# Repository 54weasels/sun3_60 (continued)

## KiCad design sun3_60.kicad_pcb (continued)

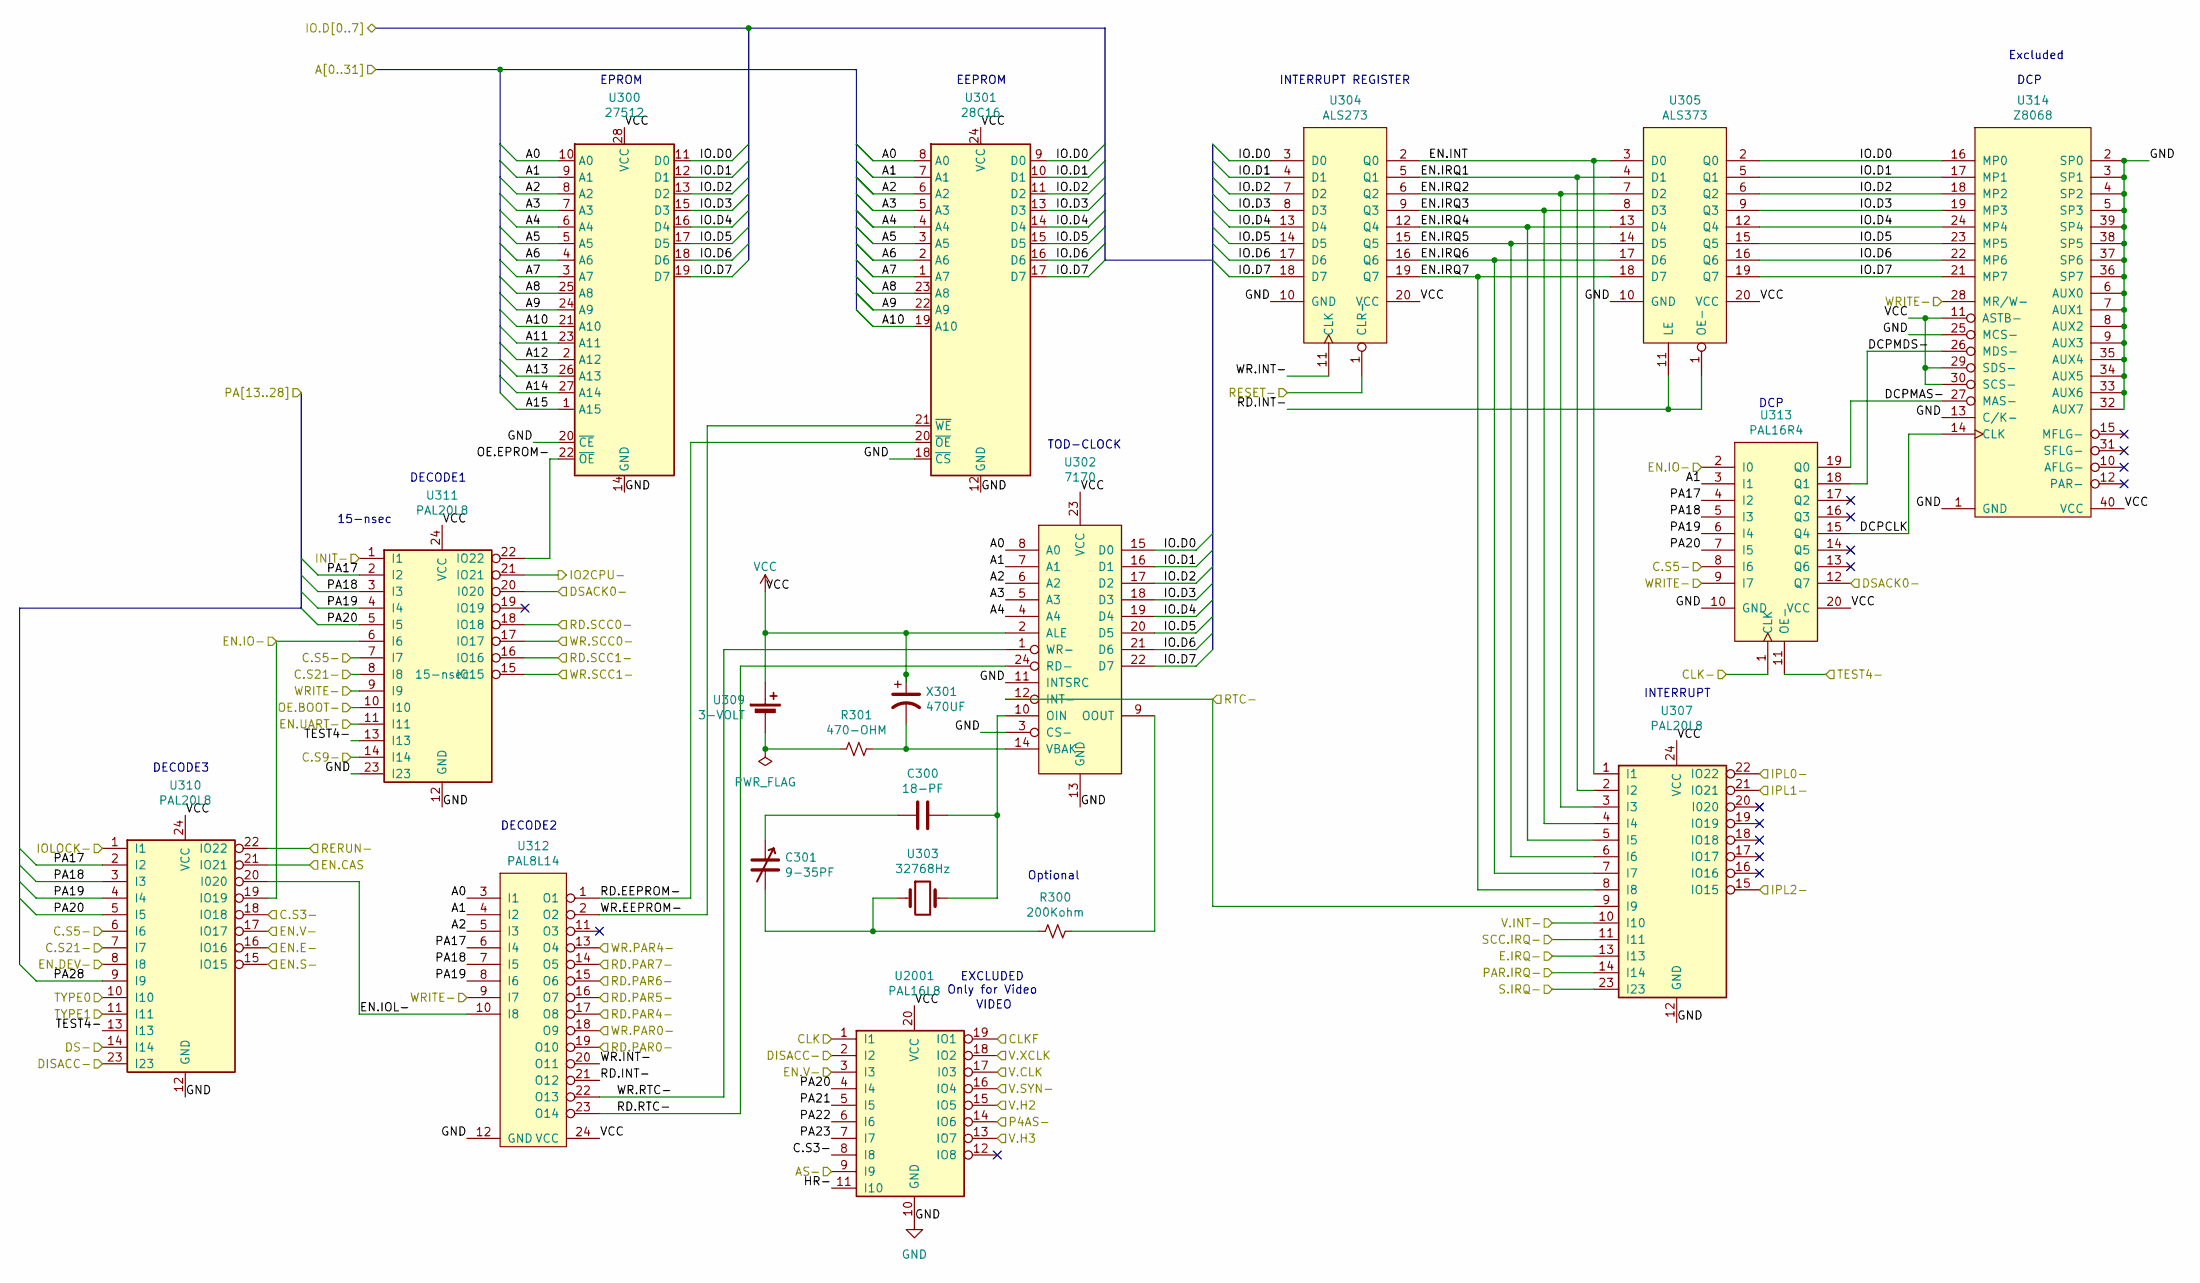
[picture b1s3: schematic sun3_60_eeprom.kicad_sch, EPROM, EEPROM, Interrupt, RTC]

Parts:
C300: 18-PF; C_Disc_D3.0mm_W2.0mm_P2.50mm
C301: 9-35PF; C_Radial_D6.3mm_H5.0mm_P2.50mm
R300: 200Kohm; R_Axial_DIN0207_L6.3mm_D2.5mm_P7.62mm_Horizontal
R301: 470-OHM; R_Axial_DIN0207_L6.3mm_D2.5mm_P7.62mm_Horizontal
U300: 27512; DIP-28_W15.24mm
U301: 28C16; DIP-24_W15.24mm
U302: 7170; DIP-24_W15.24mm
U303: 32768Hz; Crystal_AT310_D3.0mm_L10.0mm_Horizontal
U304: ALS273
U305: ALS373
U307, U310, U311: PAL20L8; DIP-24_W7.62mm
U309: 3-VOLT; Battery_Panasonic_CR2032-VS1N_Vertical_CircularHoles
U312: PAL8L14; DIP-24_W7.62mm
U313: PAL16R4; DIP-20_W7.62mm
U314: Z8068; DIP-40_W15.24mm
U2001: PAL16L8; DIP-20_W7.62mm
X301: 470UF; CP_Radial_D10.0mm_P5.00mm

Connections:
/C.S3-: U310.18 (IO18); also elsewhere on the board
/CLK-: U313.1 (CLK); also elsewhere on the board
/DISACC-: U310.23 (I23), U2001.2 (I2); also elsewhere on the board
/DS-: U310.14 (I14); also elsewhere on the board
/DSACK0-: U311.20 (I020), U313.12 (Q7); also elsewhere on the board
/E.IRQ-: U307.13 (I13); also elsewhere on the board
/EN.CAS: U310.21 (IO21); also elsewhere on the board
/EN.DEV-: U310.8 (I8); also elsewhere on the board
/EN.E-: U310.16 (IO16); also elsewhere on the board
/EN.UART-: U311.11 (I11); also elsewhere on the board
/Ethernet/A0: U300.10 (A0), U301.8 (A0), U302.8 (A0), U312.3 (I1); also elsewhere on the board
/Ethernet/A1: U300.9 (A1), U301.7 (A1), U302.7 (A1), U312.4 (I2), U313.3 (I1); also elsewhere on the board
/Ethernet/A2: U300.8 (A2), U301.6 (A2), U302.6 (A2), U312.5 (I3); also elsewhere on the board
/Ethernet/A3: U300.7 (A3), U301.5 (A3), U302.5 (A3); also elsewhere on the board
/Ethernet/A4: U300.6 (A4), U301.4 (A4), U302.4 (A4); also elsewhere on the board
/Ethernet/A5: U300.5 (A5), U301.3 (A5); also elsewhere on the board
/Ethernet/A6: U300.4 (A6), U301.2 (A6); also elsewhere on the board
/Ethernet/A7: U300.3 (A7), U301.1 (A7); also elsewhere on the board
/Ethernet/A8: U300.25 (A8), U301.23 (A8); also elsewhere on the board
/Ethernet/A9: U300.24 (A9), U301.22 (A9); also elsewhere on the board
/Ethernet/A10: U300.21 (A10), U301.19 (A10); also elsewhere on the board
/Ethernet/A11: U300.23 (A11); also elsewhere on the board
/Ethernet/A12: U300.2 (A12); also elsewhere on the board
/Ethernet/A13: U300.26 (A13); also elsewhere on the board
/Ethernet/A14: U300.27 (A14); also elsewhere on the board
/Ethernet/A15: U300.1 (A15); also elsewhere on the board
/INIT-: U311.1 (I1); also elsewhere on the board
/IO2CPU-: U311.21 (IO21); also elsewhere on the board
/IOLOCK-: U310.1 (I1); also elsewhere on the board
/IPL0-: U307.22 (IO22); also elsewhere on the board
/IPL1-: U307.21 (IO21); also elsewhere on the board
/IPL2-: U307.15 (IO15); also elsewhere on the board
/RERUN-: U310.22 (IO22); also elsewhere on the board
/RESET-: U304.1 (CLR-); also elsewhere on the board
/RTC-: U302.12 (INT-), U307.9 (I9); also elsewhere on the board
/S8A Memory/PA17: U310.2 (I2), U311.2 (I2), U312.6 (I4), U313.4 (I2); also elsewhere on the board
/S8A Memory/PA18: U310.3 (I3), U311.3 (I3), U312.7 (I5), U313.5 (I3); also elsewhere on the board
/S8A Memory/PA19: U310.4 (I4), U311.4 (I4), U312.8 (I6), U313.6 (I4); also elsewhere on the board
/S8A Memory/PA20: U310.5 (I5), U311.5 (I5), U313.7 (I5), U2001.4 (I4); also elsewhere on the board
/S8A Memory/PA28: U310.9 (I9); also elsewhere on the board
/SCC.IRQ-: U307.11 (I11); also elsewhere on the board
/SCSI 2, Parity/IO.D0: U300.11 (D0), U301.9 (D0), U302.15 (D0), U304.3 (D0), U305.2 (Q0), U314.16 (MP0); also elsewhere on the board
/SCSI 2, Parity/IO.D1: U300.12 (D1), U301.10 (D1), U302.16 (D1), U304.4 (D1), U305.5 (Q1), U314.17 (MP1); also elsewhere on the board
/SCSI 2, Parity/IO.D2: U300.13 (D2), U301.11 (D2), U302.17 (D2), U304.7 (D2), U305.6 (Q2), U314.18 (MP2); also elsewhere on the board
/SCSI 2, Parity/IO.D3: U300.15 (D3), U301.13 (D3), U302.18 (D3), U304.8 (D3), U305.9 (Q3), U314.19 (MP3); also elsewhere on the board
/SCSI 2, Parity/IO.D4: U300.16 (D4), U301.14 (D4), U302.19 (D4), U304.13 (D4), U305.12 (Q4), U314.24 (MP4); also elsewhere on the board
/SCSI 2, Parity/IO.D5: U300.17 (D5), U301.15 (D5), U302.20 (D5), U304.14 (D5), U305.15 (Q5), U314.23 (MP5); also elsewhere on the board
/SCSI 2, Parity/IO.D6: U300.18 (D6), U301.16 (D6), U302.21 (D6), U304.17 (D6), U305.16 (Q6), U314.22 (MP6); also elsewhere on the board
/SCSI 2, Parity/IO.D7: U300.19 (D7), U301.17 (D7), U302.22 (D7), U304.18 (D7), U305.19 (Q7), U314.21 (MP7); also elsewhere on the board
/SCSI 2, Parity/PAR.IRQ-: U307.14 (I14); also elsewhere on the board
/SCSI 2, Parity/RD.PAR0-: U312.19 (O10); also elsewhere on the board
/SCSI 2, Parity/RD.PAR4-: U312.17 (O8); also elsewhere on the board
/SCSI 2, Parity/RD.PAR5-: U312.16 (O7); also elsewhere on the board
/SCSI 2, Parity/RD.PAR6-: U312.15 (O6); also elsewhere on the board
/SCSI 2, Parity/RD.PAR7-: U312.14 (O5); also elsewhere on the board
/SCSI 2, Parity/WR.PAR0-: U312.18 (O9); also elsewhere on the board
/SCSI 2, Parity/WR.PAR4-: U312.13 (O4); also elsewhere on the board
/TEST4-: U310.13 (I13), U311.13 (I13), U313.11 (OE-); also elsewhere on the board
/V.INT-: U307.10 (I10); also elsewhere on the board
/WRITE-: U311.9 (I9), U312.9 (I7), U313.9 (I7), U314.28 (MR/W-); also elsewhere on the board
/sun3_60_cpu/C.S5-: U310.6 (I6), U311.7 (I7), U313.8 (I6); also elsewhere on the board
/sun3_60_cpu/C.S9-: U311.14 (I14); also elsewhere on the board
/sun3_60_cpu/C.S21-: U310.7 (I7), U311.8 (I8); also elsewhere on the board
/sun3_60_cpu/OE.BOOT-: U311.10 (I10); also elsewhere on the board
/sun3_60_eeprom/DCPCLK: U313.15 (Q4), U314.14 (CLK)
/sun3_60_eeprom/DCPMAS-: U313.19 (Q0), U314.27 (MAS-)
/sun3_60_eeprom/DCPMDS-: U313.18 (Q1), U314.26 (MDS-)
/sun3_60_eeprom/EN.INT: U304.2 (Q0), U305.3 (D0), U307.1 (I1)
/sun3_60_eeprom/EN.IO-: U310.19 (IO19), U311.6 (I6), U313.2 (I0)
/sun3_60_eeprom/EN.IOL-: U310.20 (I020), U312.10 (I8)
/sun3_60_eeprom/EN.IRQ1: U304.5 (Q1), U305.4 (D1), U307.2 (I2)
/sun3_60_eeprom/EN.IRQ2: U304.6 (Q2), U305.7 (D2), U307.3 (I3)
/sun3_60_eeprom/EN.IRQ3: U304.9 (Q3), U305.8 (D3), U307.4 (I4)
/sun3_60_eeprom/EN.IRQ4: U304.12 (Q4), U305.13 (D4), U307.5 (I5)
/sun3_60_eeprom/EN.IRQ5: U304.15 (Q5), U305.14 (D5), U307.6 (I6)
/sun3_60_eeprom/EN.IRQ6: U304.16 (Q6), U305.17 (D6), U307.7 (I7)
/sun3_60_eeprom/EN.IRQ7: U304.19 (Q7), U305.18 (D7), U307.8 (I8)
/sun3_60_eeprom/EN.S-: U310.15 (IO15)
/sun3_60_eeprom/EN.V-: U310.17 (IO17), U2001.3 (I3)
/sun3_60_eeprom/OE.EPROM-: U300.22 (~OE), U311.22 (IO22)
/sun3_60_eeprom/RD.EEPROM-: U301.20 (~OE), U312.1 (O1)
/sun3_60_eeprom/RD.INT-: U305.1 (OE-), U305.11 (LE), U312.21 (O12)
/sun3_60_eeprom/RD.RTC-: U302.24 (RD-), U312.23 (O14)
/sun3_60_eeprom/RD.SCC0-: U311.18 (IO18)
/sun3_60_eeprom/RD.SCC1-: U311.16 (IO16); also elsewhere on the board
/sun3_60_eeprom/S.IRQ-: U307.23 (I23)
/sun3_60_eeprom/TYPE0: U310.10 (I10); also elsewhere on the board
/sun3_60_eeprom/TYPE1: U310.11 (I11); also elsewhere on the board
/sun3_60_eeprom/WR.EEPROM-: U301.21 (~WE), U312.2 (O2)
/sun3_60_eeprom/WR.INT-: U304.11 (CLK), U312.20 (O11)
/sun3_60_eeprom/WR.RTC-: U302.1 (WR-), U312.22 (O13)
/sun3_60_eeprom/WR.SCC0-: U311.17 (IO17)
/sun3_60_eeprom/WR.SCC1-: U311.15 (IO15); also elsewhere on the board
GND: U300.14 (GND), U300.20 (~CE), U301.12 (GND), U301.18 (~CS), U302.3 (CS-), U302.11 (INTSRC), U302.13 (GND), U304.10 (GND), U305.10 (GND), U307.12 (GND), U310.12 (GND), U311.12 (GND), U311.23 (I23), U312.12 (GND), U313.10 (GND), U314.1 (GND), U314.2 (SP0), U314.3 (SP1), U314.4 (SP2), U314.5 (SP3), U314.6 (AUX0), U314.7 (AUX1), U314.8 (AUX2), U314.9 (AUX3), U314.13 (C/K-), U314.25 (MCS-), U314.32 (AUX7), U314.33 (AUX6), U314.34 (AUX5), U314.35 (AUX4), U314.36 (SP7), U314.37 (SP6), U314.38 (SP5), U314.39 (SP4), U2001.10 (GND); also elsewhere on the board
unnamed: C300.2, C301.1
unnamed: C301.2, R300.2, U303.1
unnamed: C300.1, U302.10 (OIN), U303.2
unnamed: R300.1, U302.9 (OOUT)
unnamed: R301.1, U302.14 (VBAK), X301.2
unnamed: R301.2, U309.2 (-)
VCC: U300.28 (VCC), U301.24 (VCC), U302.2 (ALE), U302.23 (VCC), U304.20 (VCC), U305.20 (VCC), U307.24 (VCC), U309.1 (+), U310.24 (VCC), U311.24 (VCC), U312.24 (VCC), U313.20 (VCC), U314.11 (ASTB-), U314.29 (SDS-), U314.30 (SCS-), U314.40 (VCC), U2001.20 (VCC), X301.1; also elsewhere on the board

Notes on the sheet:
DECODE2
VIDEO
INTERRUPT
TOD-CLOCK
DCP
DECODE1
EPROM
DECODE3
INTERRUPT REGISTER
15-nsec
Optional
Excluded
EXCLUDED Only for Video
EEPROM

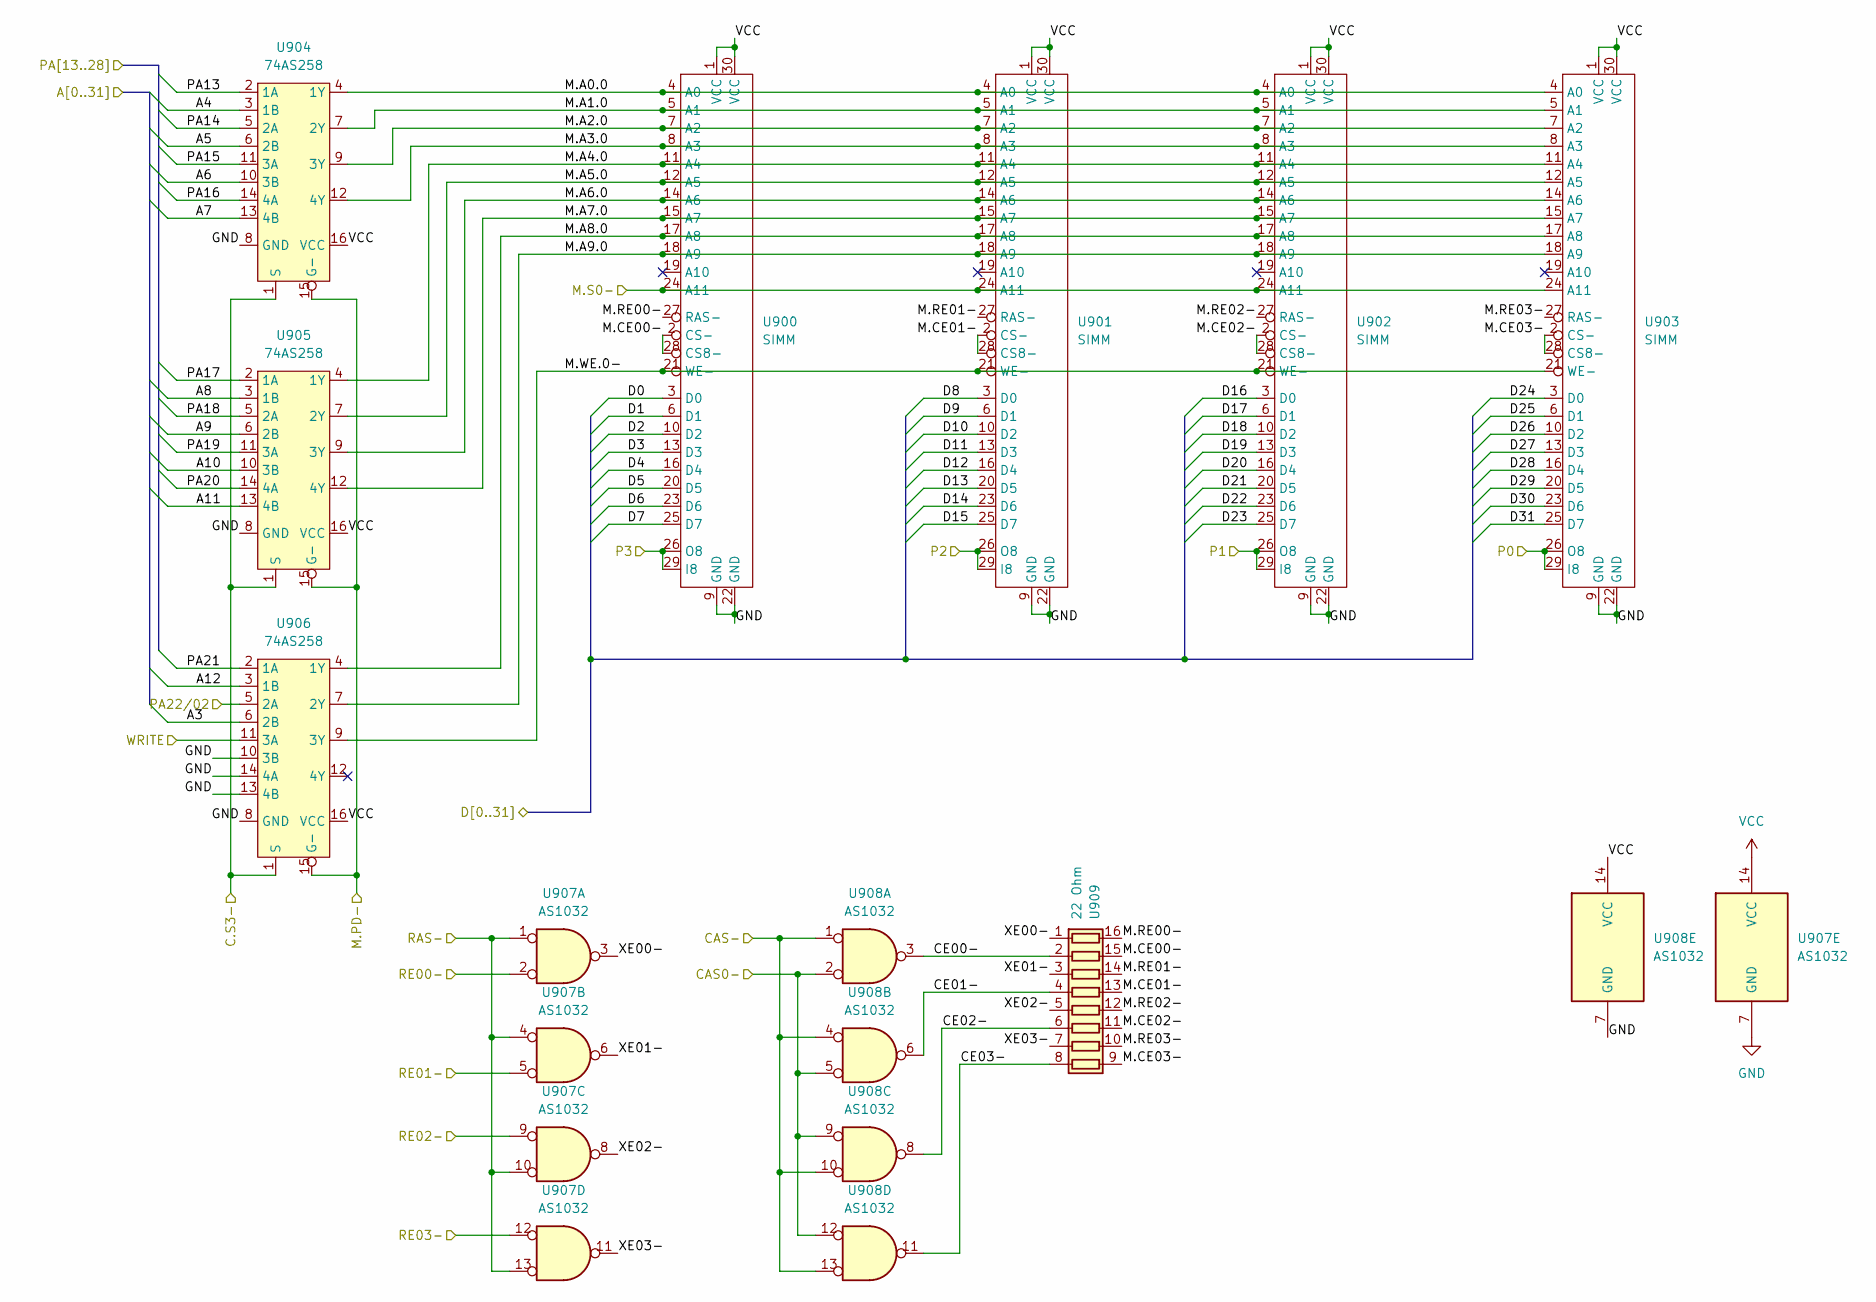
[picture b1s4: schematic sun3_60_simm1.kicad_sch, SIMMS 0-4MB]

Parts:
U900, U901, U902, U903: SIMM; PinHeader_1x30_P2.54mm_Vertical
U904, U905, U906: 74AS258; DIP-16_W7.62mm
U907, U908: AS1032; DIP-14_W7.62mm
U909: 22 Ohm; DIP-16_W7.62mm

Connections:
/C.S3: U904.1 (S), U905.1 (S), U906.1 (S); also elsewhere on the board
/CAS-: U908.1, U908.4, U908.10, U908.13; also elsewhere on the board
/Ethernet/A3: U906.6 (2B); also elsewhere on the board
/Ethernet/A4: U904.3 (1B); also elsewhere on the board
/Ethernet/A5: U904.6 (2B); also elsewhere on the board
/Ethernet/A6: U904.10 (3B); also elsewhere on the board
/Ethernet/A7: U904.13 (4B); also elsewhere on the board
/Ethernet/A8: U905.3 (1B); also elsewhere on the board
/Ethernet/A9: U905.6 (2B); also elsewhere on the board
/Ethernet/A10: U905.10 (3B); also elsewhere on the board
/Ethernet/A11: U905.13 (4B); also elsewhere on the board
/Ethernet/A12: U906.3 (1B); also elsewhere on the board
/P0: U903.26 (O8), U903.29 (I8); also elsewhere on the board
/P1: U902.26 (O8), U902.29 (I8); also elsewhere on the board
/P2: U901.26 (O8), U901.29 (I8); also elsewhere on the board
/P3: U900.26 (O8), U900.29 (I8); also elsewhere on the board
/READ-: U906.11 (3A); also elsewhere on the board
/S8A Memory/CAS0-: U908.2, U908.5, U908.9, U908.12; also elsewhere on the board
/S8A Memory/M.PD-: U904.15 (G-), U905.15 (G-), U906.15 (G-); also elsewhere on the board
/S8A Memory/PA13: U904.2 (1A); also elsewhere on the board
/S8A Memory/PA14: U904.5 (2A); also elsewhere on the board
/S8A Memory/PA15: U904.11 (3A); also elsewhere on the board
/S8A Memory/PA16: U904.14 (4A); also elsewhere on the board
/S8A Memory/PA17: U905.2 (1A); also elsewhere on the board
/S8A Memory/PA18: U905.5 (2A); also elsewhere on the board
/S8A Memory/PA19: U905.11 (3A); also elsewhere on the board
/S8A Memory/PA20: U905.14 (4A); also elsewhere on the board
/S8A Memory/PA21: U906.2 (1A); also elsewhere on the board
/S8A Memory/PA22/02: U906.5 (2A); also elsewhere on the board
/S8A Memory/RAS-: U907.1, U907.4, U907.10, U907.13; also elsewhere on the board
/S8A Memory/RE00-: U907.2; also elsewhere on the board
/S8A Memory/RE01-: U907.5; also elsewhere on the board
/S8A Memory/RE02-: U907.9; also elsewhere on the board
/S8A Memory/RE03-: U907.12; also elsewhere on the board
/SIMMs 1/CE00-: U908.3, U909.2 (R2.1)
/SIMMs 1/CE01-: U908.6, U909.4 (R4.1)
/SIMMs 1/CE02-: U908.8, U909.6 (R6.1)
/SIMMs 1/CE03-: U908.11, U909.8 (R8.1)
/SIMMs 1/M.A0.0: U900.4 (A0), U901.4 (A0), U902.4 (A0), U903.4 (A0), U904.4 (1Y)
/SIMMs 1/M.A1.0: U900.5 (A1), U901.5 (A1), U902.5 (A1), U903.5 (A1), U904.7 (2Y)
/SIMMs 1/M.A2.0: U900.7 (A2), U901.7 (A2), U902.7 (A2), U903.7 (A2), U904.9 (3Y)
/SIMMs 1/M.A3.0: U900.8 (A3), U901.8 (A3), U902.8 (A3), U903.8 (A3), U904.12 (4Y)
/SIMMs 1/M.A4.0: U900.11 (A4), U901.11 (A4), U902.11 (A4), U903.11 (A4), U905.4 (1Y)
/SIMMs 1/M.A5.0: U900.12 (A5), U901.12 (A5), U902.12 (A5), U903.12 (A5), U905.7 (2Y)
/SIMMs 1/M.A6.0: U900.14 (A6), U901.14 (A6), U902.14 (A6), U903.14 (A6), U905.9 (3Y)
/SIMMs 1/M.A7.0: U900.15 (A7), U901.15 (A7), U902.15 (A7), U903.15 (A7), U905.12 (4Y)
/SIMMs 1/M.A8.0: U900.17 (A8), U901.17 (A8), U902.17 (A8), U903.17 (A8), U906.4 (1Y)
/SIMMs 1/M.A9.0: U900.18 (A9), U901.18 (A9), U902.18 (A9), U903.18 (A9), U906.7 (2Y)
/SIMMs 1/M.CE00-: U900.2 (CS-), U900.28 (CS8-), U909.15 (R2.2)
/SIMMs 1/M.CE01-: U901.2 (CS-), U901.28 (CS8-), U909.13 (R4.2)
/SIMMs 1/M.CE02-: U902.2 (CS-), U902.28 (CS8-), U909.11 (R6.2)
/SIMMs 1/M.CE03-: U903.2 (CS-), U903.28 (CS8-), U909.9 (R8.2)
/SIMMs 1/M.RE00-: U900.27 (RAS-), U909.16 (R1.2)
/SIMMs 1/M.RE01-: U901.27 (RAS-), U909.14 (R3.2)
/SIMMs 1/M.RE02-: U902.27 (RAS-), U909.12 (R5.2)
/SIMMs 1/M.RE03-: U903.27 (RAS-), U909.10 (R7.2)
/SIMMs 1/M.WE.0-: U900.21 (WE-), U901.21 (WE-), U902.21 (WE-), U903.21 (WE-), U906.9 (3Y)
/SIMMs 1/XE00-: U907.3, U909.1 (R1.1)
/SIMMs 1/XE01-: U907.6, U909.3 (R3.1)
/SIMMs 1/XE02-: U907.8, U909.5 (R5.1)
/SIMMs 1/XE03-: U907.11, U909.7 (R7.1)
/sun3_60_cpu/D0: U900.3 (D0); also elsewhere on the board
/sun3_60_cpu/D1: U900.6 (D1); also elsewhere on the board
/sun3_60_cpu/D2: U900.10 (D2); also elsewhere on the board
/sun3_60_cpu/D3: U900.13 (D3); also elsewhere on the board
/sun3_60_cpu/D4: U900.16 (D4); also elsewhere on the board
/sun3_60_cpu/D5: U900.20 (D5); also elsewhere on the board
/sun3_60_cpu/D6: U900.23 (D6); also elsewhere on the board
/sun3_60_cpu/D7: U900.25 (D7); also elsewhere on the board
/sun3_60_cpu/D8: U901.3 (D0); also elsewhere on the board
/sun3_60_cpu/D9: U901.6 (D1); also elsewhere on the board
/sun3_60_cpu/D10: U901.10 (D2); also elsewhere on the board
/sun3_60_cpu/D11: U901.13 (D3); also elsewhere on the board
/sun3_60_cpu/D12: U901.16 (D4); also elsewhere on the board
/sun3_60_cpu/D13: U901.20 (D5); also elsewhere on the board
/sun3_60_cpu/D14: U901.23 (D6); also elsewhere on the board
/sun3_60_cpu/D15: U901.25 (D7); also elsewhere on the board
/sun3_60_cpu/D16: U902.3 (D0); also elsewhere on the board
/sun3_60_cpu/D17: U902.6 (D1); also elsewhere on the board
/sun3_60_cpu/D18: U902.10 (D2); also elsewhere on the board
/sun3_60_cpu/D19: U902.13 (D3); also elsewhere on the board
/sun3_60_cpu/D20: U902.16 (D4); also elsewhere on the board
/sun3_60_cpu/D21: U902.20 (D5); also elsewhere on the board
/sun3_60_cpu/D22: U902.23 (D6); also elsewhere on the board
/sun3_60_cpu/D23: U902.25 (D7); also elsewhere on the board
/sun3_60_cpu/D24: U903.3 (D0); also elsewhere on the board
/sun3_60_cpu/D25: U903.6 (D1); also elsewhere on the board
/sun3_60_cpu/D26: U903.10 (D2); also elsewhere on the board
/sun3_60_cpu/D27: U903.13 (D3); also elsewhere on the board
/sun3_60_cpu/D28: U903.16 (D4); also elsewhere on the board
/sun3_60_cpu/D29: U903.20 (D5); also elsewhere on the board
/sun3_60_cpu/D30: U903.23 (D6); also elsewhere on the board
/sun3_60_cpu/D31: U903.25 (D7); also elsewhere on the board
GND: U900.9 (GND), U900.22 (GND), U900.24 (A11), U901.9 (GND), U901.22 (GND), U901.24 (A11), U902.9 (GND), U902.22 (GND), U902.24 (A11), U903.9 (GND), U903.22 (GND), U903.24 (A11), U904.8 (GND), U905.8 (GND), U906.8 (GND), U906.10 (3B), U906.13 (4B), U906.14 (4A), U907.7 (GND), U908.7 (GND); also elsewhere on the board
VCC: U900.1 (VCC), U900.30 (VCC), U901.1 (VCC), U901.30 (VCC), U902.1 (VCC), U902.30 (VCC), U903.1 (VCC), U903.30 (VCC), U904.16 (VCC), U905.16 (VCC), U906.16 (VCC), U907.14 (VCC), U908.14 (VCC); also elsewhere on the board

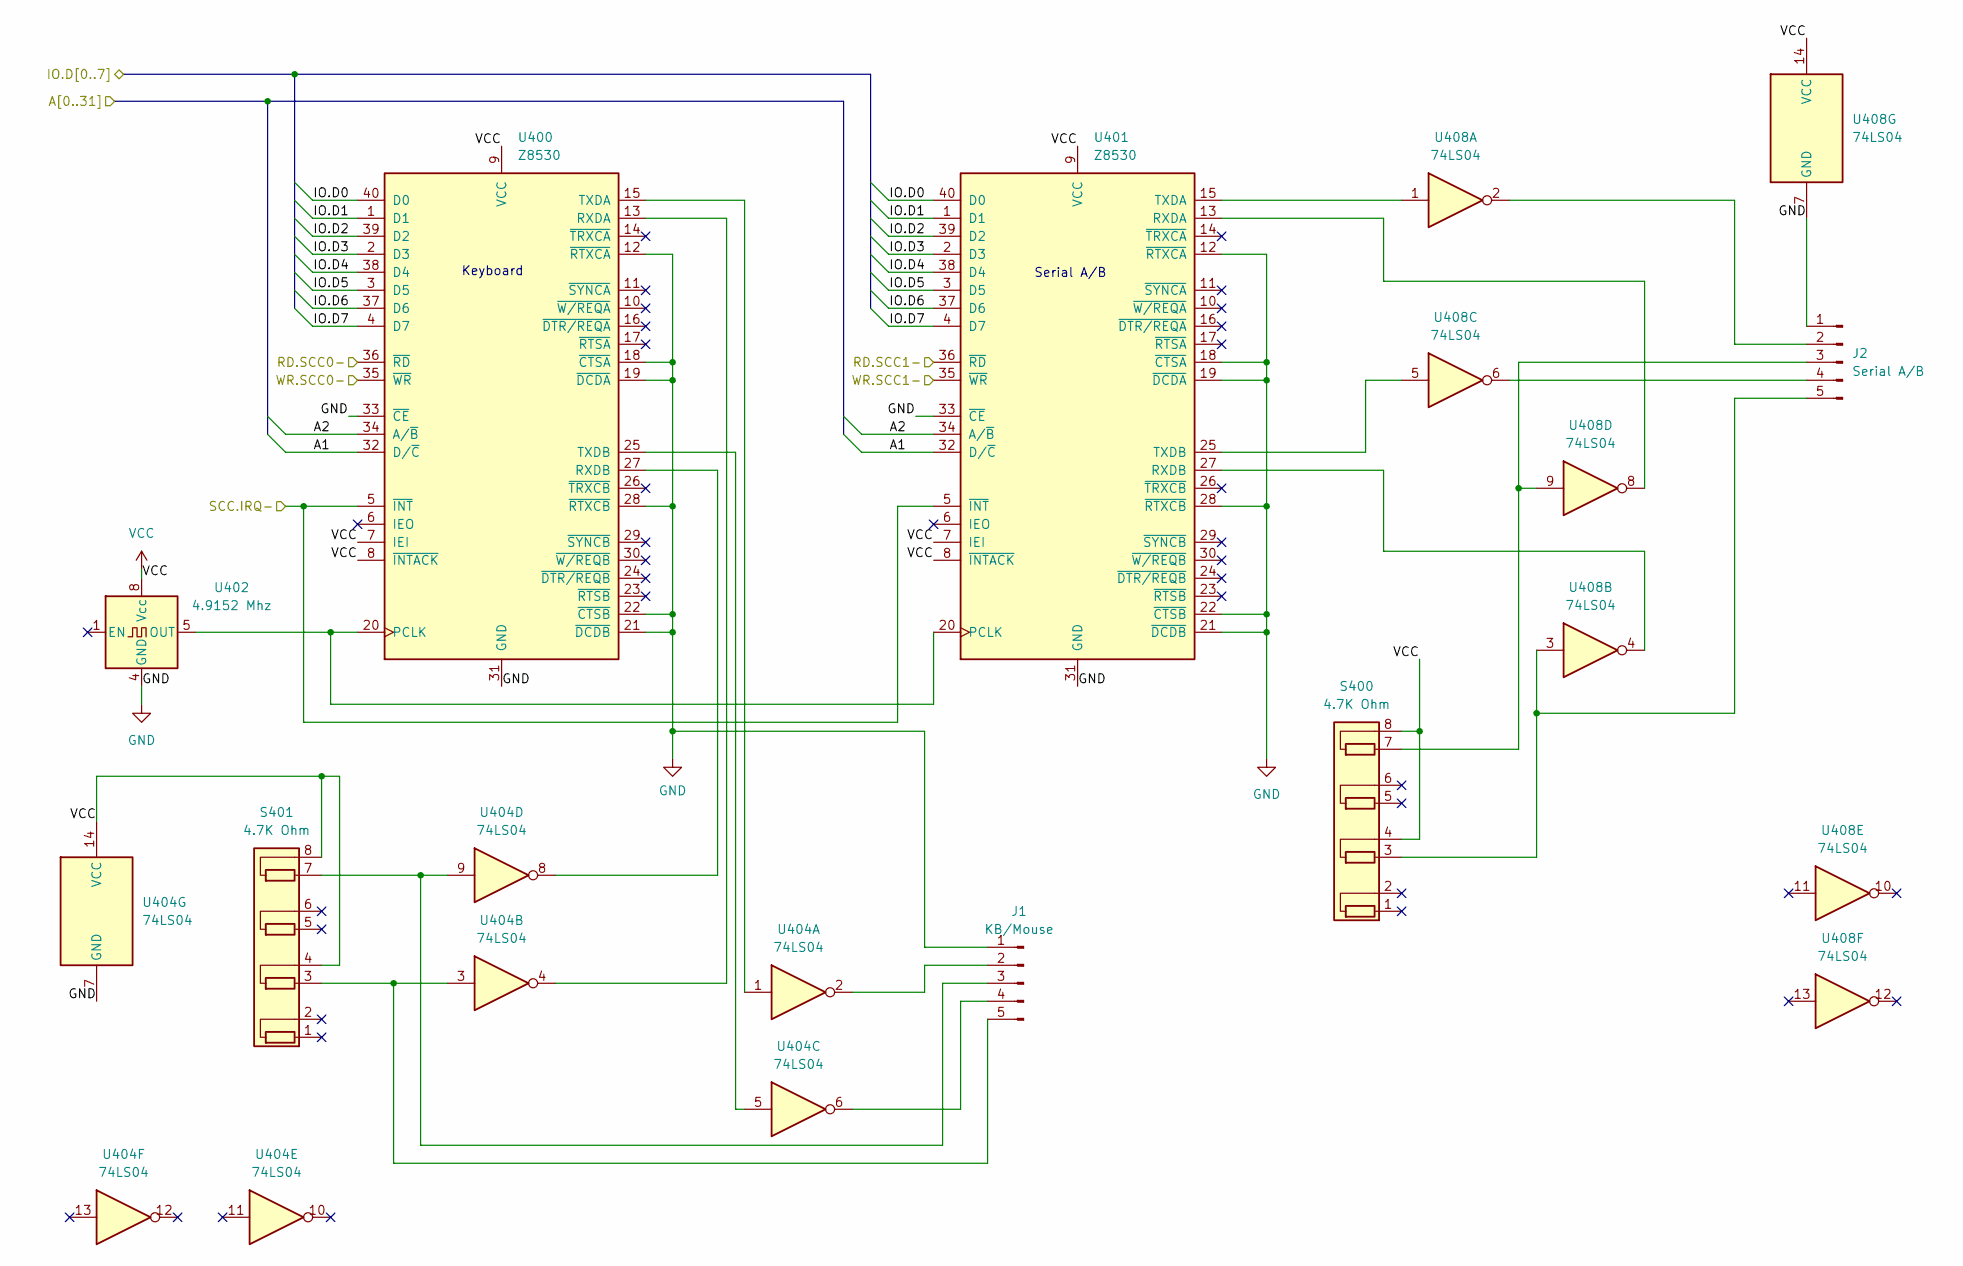
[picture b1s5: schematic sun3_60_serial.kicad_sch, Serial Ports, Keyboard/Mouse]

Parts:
J1: KB/Mouse; PinHeader_1x05_P2.54mm_Vertical
J2: Serial A/B; PinHeader_1x05_P2.54mm_Vertical
S400, S401: 4.7K Ohm; R_Array_SIP8
U400, U401: Z8530; DIP-40_W15.24mm
U402: 4.9152 Mhz; Oscillator_DIP-8
U404, U408: 74LS04; DIP-14_W7.62mm

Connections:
/Ethernet/A1: U400.32 (D/~C), U401.32 (D/~C); also elsewhere on the board
/Ethernet/A2: U400.34 (A/~B), U401.34 (A/~B); also elsewhere on the board
/SCC.IRQ-: U400.5 (~INT), U401.5 (~INT); also elsewhere on the board
/SCSI 2, Parity/IO.D0: U400.40 (D0), U401.40 (D0); also elsewhere on the board
/SCSI 2, Parity/IO.D1: U400.1 (D1), U401.1 (D1); also elsewhere on the board
/SCSI 2, Parity/IO.D2: U400.39 (D2), U401.39 (D2); also elsewhere on the board
/SCSI 2, Parity/IO.D3: U400.2 (D3), U401.2 (D3); also elsewhere on the board
/SCSI 2, Parity/IO.D4: U400.38 (D4), U401.38 (D4); also elsewhere on the board
/SCSI 2, Parity/IO.D5: U400.3 (D5), U401.3 (D5); also elsewhere on the board
/SCSI 2, Parity/IO.D6: U400.37 (D6), U401.37 (D6); also elsewhere on the board
/SCSI 2, Parity/IO.D7: U400.4 (D7), U401.4 (D7); also elsewhere on the board
/sun3_60_eeprom/RD.SCC1-: U401.36 (~RD); also elsewhere on the board
/sun3_60_eeprom/WR.SCC1-: U401.35 (~WR); also elsewhere on the board
GND: J1.1, J2.1, U400.12 (~RTXCA), U400.18 (~CTSA), U400.19 (~DCDA), U400.21 (~DCDB), U400.22 (~CTSB), U400.28 (~RTXCB), U400.31 (GND), U400.33 (~CE), U401.12 (~RTXCA), U401.18 (~CTSA), U401.19 (~DCDA), U401.21 (~DCDB), U401.22 (~CTSB), U401.28 (~RTXCB), U401.31 (GND), U401.33 (~CE), U402.4 (GND), U404.7 (GND), U408.7 (GND); also elsewhere on the board
unnamed: J1.2, U404.2
unnamed: J1.3, S401.7 (R4.1), U404.9
unnamed: J1.4, U404.6
unnamed: J1.5, S401.3 (R2.1), U404.3
unnamed: J2.2, U408.2
unnamed: J2.3, S400.7 (R4.1), U408.9
unnamed: J2.4, U408.6
unnamed: J2.5, S400.3 (R2.1), U408.3
unnamed: U400.13 (RXDA), U404.4
unnamed: U400.15 (TXDA), U404.1
unnamed: U400.25 (TXDB), U404.5
unnamed: U400.27 (RXDB), U404.8
unnamed: U400.20 (PCLK), U401.20 (PCLK), U402.5 (OUT)
unnamed: U401.13 (RXDA), U408.8
unnamed: U401.27 (RXDB), U408.4
unnamed: U401.15 (TXDA), U408.1
unnamed: U401.25 (TXDB), U408.5
VCC: S400.4 (R2.2), S400.8 (R4.2), S401.4 (R2.2), S401.8 (R4.2), U400.7 (IEI), U400.8 (~INTACK), U400.9 (VCC), U401.7 (IEI), U401.8 (~INTACK), U401.9 (VCC), U402.8 (Vcc), U404.14 (VCC), U408.14 (VCC); also elsewhere on the board

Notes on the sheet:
Keyboard
Serial A/B
